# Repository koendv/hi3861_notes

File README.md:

# Hi3861 Notes

[Hi3861](https://www.hisilicon.com/en/products/smart-iot/ShortRangeWirelessIOT/Hi3861V100) is a 32-bit risc-v microcontroller, made by Huawei/HiSilicon.

- 160 MHz
- 288 kbyte rom
- 352 kbyte ram in total, 280 kbyte ram available for user programs
- 2 mbyte flash
- WiFi

## block diagram

This is a block diagram of the Hi3861 processor.
External components are a 40MHz crystal, a 32768 Hz crystal, and a pcb antenna. Flash memory is connected via spi. The HI3861 has 2 Mbyte flash memory.

The HI3861 shares die with the HI3881 wifi video camera. The HI3881 IP camera version does not have spi flash memory. The HI3881 runs software from rom.

## memory map

This is the memory map of the Hi3861. 保留 = reserved.

- RAM (rx): ORIGIN = 0x000D8000, LENGTH = 280K
- ROM  (rx):     ORIGIN = 0x003B8000, LENGTH = 288K
- FLASH (rwx):  ORIGIN = 0x00400000, LENGTH = 16M

16 Mbyte address space is mapped to spi flash, but the HI3861 spi flash is only 2 Mbyte in size.

## JTAG

## pins

pin | jtag ||
---|---|---|
IO00|JTAG_TDO|
IO01|JTAG_TCK|
IO02|JTAG_TRSTN|
IO03|JTAG_TDI|
IO04|JTAG_TMS|
IO06|JTAG_MODE|
IO08|JTAG_ENABLE|Pull high

If pin IO8 is low at power-up, pins IO0...IO4 are normal GPIO pins.
If pin IO8 is high at power-up, pins IO0...IO4 are used for JTAG.

If JTAG_ENABLE is high at power-up, pins IO03, IO04 are used for JTAG.  If JTAG_ENABLE is low at power-up, pins IO03, IO04 are used as console serial port RX, TX pins. Conflict is possible if using usb serial and JTAG at the same time.

## hi3861 start up mode

Pin|Default state|Low level|High level
---|---|---|---
IO2/REFCLK_FREQ_STATUS|Pull down|40MHz (Default) |24MHz
IO6/JTAG_MODE|Pull down|Normal function mode (Default) |DFT Test mode
IO8/JTAG_ENABLE|Pull down|Ordinary IO (Default) |JTAG enable

## jtag adapter

|||
|---|---|
|front|back|

A small circuit is needed to enable the JTAG interface. The adapter board plugs in on the back of the Hi3861 module. This adapter board can be soldered by hand.

- [schematic](hi3861-jtag/hi3861-jtag_sch.pdf)
- [kicad pcb design](hi3861-jtag)

## Boot

The boot process of Hi3861 consists with three parts: romboot, flashboot and kernel (user code, or the OS itself).

1. The fixed **romboot** verifies the **flashboot** at `FLASH_BASE`, copies the flashboot to `0x10A000` (which is actually `CPU_RAM_BASE + 200KB`) and executes. Since the first 64 bytes in the bootable image is the signature header, the actual entry is `0x10A040`
2. The **flashboot** then verifies and boots the **kernel** at `FLASH_BASE + 0xD3C0`.

## Build

A full build of LiteOS generates several images. Finally a `Hi3861_demo_allinone.bin` can be imported to the HiBurn tool to flash. Here is a flow chart of the build progress:

Though not documented, the signature header is simple. There is an open source signing tool in Python: [sign_bin.py](https://github.com/xingrz/hal_hisilicon/blob/319fce6760d25510ffae30f06c8d2190db636db2/hi3861/boot/sign_bin.py)

## tools

Tools to flash firmware: hiburn, openocd, jlink.

### hiburn

The tool to download firmware to the HI3861/HI3881 through the serial port is called **hiburn**. There is a hiburn from Huawei, and there are open source versions. These are different tools that share the same name.

- [Hiburn](tools/) is a Windows tool from Huawei for downloading firmware via the serial port.
- The Zephyr project has an [open source alternative  for Hi3861](https://github.com/xingrz/zephyr/blob/87f33dc624405e1a0e99fb78715cfd644421106b/scripts/west_commands/runners/hiburn.py).

The protocol to flash Hi3861 is a combination of a private command procotol and [Ymodem](https://en.wikipedia.org/wiki/YMODEM). Though the client side (HiBurn) is not open source, we can see how the protocol looks from the server side: [loaderboot](https://gitee.com/openharmony/device_soc_hisilicon/blob/master/hi3861v100/sdk_liteos/boot/loaderboot/common/cmd_loop.c) from the LiteOS/OpenHarmony SDK. Just like the flashboot, the entry of the loaderboot is at `0x10A040`.

For hiburn to work, LiteOS or OpenHarmony needs to contain the u-boot feature.

### openocd

The [openocd directory](openocd) contains configuration files for the open source tool [openocd](https://openocd.org/). This is what I use to download firmware to a Hi3861 board. Needs a FT2232 module, and the JTAG adapter above.

To build openocd with risc-v extensions:
```
sudo apt-get build-dep openocd
git clone https://github.com/riscv/riscv-openocd
cd riscv-openocd
./bootstrap
./configure --prefix=/opt/riscv-openocd
make
make install
```
To use openocd as gdb server:

```
/opt/riscv-openocd/bin/openocd -f ./interface/hi-ft2232d-ftdi-jtag.cfg -f ./target/hi3861-jtag.cfg
...
Info : clock speed 500 kHz
Info : JTAG tap: hi3861.cpu tap/device found: 0x0000076d (mfg: 0x3b6 (HiSilicon Technologies), part: 0x0000, ver: 0x0)
Info : [hi3861.cpu] datacount=1 progbufsize=3
Info : Disabling abstract command reads from CSRs.
Info : Examined RISC-V core; found 1 harts
Info :  hart 0: XLEN=32, misa=0x40901104
[hi3861.cpu] Target successfully examined.
Info : starting gdb server for hi3861.cpu on 3333
Info : Listening on port 3333 for gdb connections
load_bin
Info : Listening on port 6666 for tcl connections
Info : Listening on port 4444 for telnet connections
```
In another terminal:
```
/opt/riscv-binutils-gdb/bin/riscv-elf-gdb -q
(gdb) target extended-remote :3333
(gdb) file firmware.elf
(gdb) load
```
### ft2232

[FT2232HL](https://ftdichip.com/products/ft2232hl/) is an ic that interfaces between between usb and uart, jtag, swd, spi, or i2c. FT2232 is well supported by OpenOCD. The FT2232 board above has the advantage that the board has the same pinout as a Segger JLink, so you can use the same cable for both OpenOCD and JLink. [FT2232HL Board Schematic V3](ft2232hl/FT2232HL%20Board%20sch%20V3.pdf).

### jlink

The [jlink directory](jlink) contains a script for the [Segger JLink](https://www.segger.com/products/debug-probes/j-link/) debugger. This script can be modified to flash firmware to a Hi3861.

```
JLink.exe -device RISC-V -Speed 2000 -IF JTAG -jtagconf -1,-1 jlinkBurner.txt
```
Under linux:
```
 $ rlfe /opt/jlink/JLinkExe -device RV32 -if JTAG -speed 1000 -jtagconf -1,-1 -AutoConnect 1
Connecting to target via JTAG
ConfigTargetSettings() start
ConfigTargetSettings() end
TotalIRLen = ?, IRPrint = 0x..000000000000000000000000
ConfigTargetSettings() start
ConfigTargetSettings() end
TotalIRLen = 5, IRPrint = 0x01
JTAG chain detection found 1 devices:
 #0 Id: 0x0000076D, IRLen: 05, HiSilicon RV32
Debug architecture:
  RISC-V debug: 0.13
  AddrBits: 7
  DataBits: 32
  IdleClks: 5
Memory access:
  Via system bus: No
  Via ProgBuf: Yes (3 ProgBuf entries)
  Via abstract command (AAM): May be tried as last resort
DataBuf: 1 entries
  autoexec[0] implemented: Yes
Detected: RV32 core
CSR access via abs. commands: No
Temp. halted CPU for NumHWBP detection
HW instruction/data BPs: 4
Support set/clr BPs while running: No
HW data BPs trigger before execution of inst
BG memory access support: No
RISC-V identified.
J-Link>
```
jlink has a good implementation of the risc-v debug interface, but support to flash Hi3861 processors is not built in. Keep the JTAG cable short - 6cm or less.

### black magic probe

[Black magic probe](https://github.com/blackmagic-debug/blackmagic) is an open source debugger for arm processors. risc-v on bmp is part of the development sources, but not yet of the release. The Hi3861 is recognized, but support for reading and writing Hi3861 flash is missing.

## toolchain

Compile the riscv toolchain from source:

```
git clone --recursive https://github.com/riscv/riscv-gnu-toolchain
cd riscv-gnu-toolchain/
mkdir build
cd build/
../configure --prefix=/opt/riscv32 --with-arch=rv32im --with-abi=ilp32
make
```

The `riscv32-unknown-elf` toolchain works fine. The `riscv64-zephyr-elf` from [Zephyr SDK](https://github.com/zephyrproject-rtos/sdk-ng/releases/tag/v0.16.0) works fine, too (I prefer it since it runs on my MacBook Pro :p ).

The Hi3861's CPU is actually a RISC-V Privilege CPU with instruction set extension-M plus extension-C and Zicsr. While compiling with the Zephyr GCC, `-march=rv32imc` should be changed to `-march=rv32imc_zicsr`.

## gdb

gdb, the companion debugger for gcc. Build gdb for risc-v from source:

```
git clone https://github.com/riscv/riscv-binutils-gdb.git
cd riscv-binutils-gdb
patch -p1 < risc-v-gdb.patch
cd ..
mkdir build
cd build
../riscv-binutils-gdb/configure --prefix=/opt/riscv-binutils-gdb/ --target=riscv-elf --program-prefix=riscv-elf-
make all
sudo make install
```

If you start a 64-bit gdb, and connect to a 32-bit target, it may be necessary to specify architecture first:

```
(gdb) set architecture riscv:rv32
```
## operating systems

The Hi3861 is supported by two Huawei operating systems: LiteOS and OpenHarmony. There is also open source for the Zephyr RTOS and the rust language.

The sdk can be compiled with [riscv32-unknown-elf-gcc](https://device.harmonyos.com/en/docs/documentation/guide/quickstart-lite-steps-hi3861-setting-0000001105989316) or with hcc_riscv32, a patched gcc 7.3.  Compared to standard *riscv32-unknown-elf-gcc*, the hcc_riscv32 compiler has extensions for faster interrupts and more compact code:

- "compressed load-byte-unsigned" *lbu* and "store byte" *sb* instructions. Compiler option ``-Wa,-enable-c-lbu-sb``
- "long load immediate" *lli* instruction in 6 bytes, saves 2 bytes. Compiler option ``-femit-lli``
- "store multiple, increment after" *stmia* and "load multiple, increment after" *ldmia* instructions. Pushes/pops register sets on the stack in a single instruction, fast. Used in trap handler.
- merge multiple load and store instructions into "load multiple" *ldm* and "store multiple" *stm* instructions. Compiler option ``-fldm-stm-optimize``

These extensions to standard risc-v are discussed in [Perotti](doc/CARRV2020_paper_12_Perotti.pdf).

## zephyr

[xingrz](https://xingrz.me/) is porting [Zephyr RTOS to Hi3861](https://github.com/xingrz/zephyr/commits/hi3861-dev).

## rust

Rust application example for hi3861. Install rust from [rustup](https://rustup.rs/).
```
git clone https://gitee.com/luojia65/hihope-hi3861-example
cd hihope-hi3861-example
cargo build
```
Check binary:

```
$ /opt/riscv-binutils-gdb/bin/riscv-elf-objdump -f target/riscv32imac-unknown-none-elf/debug/hihope-hi3861-example
target/riscv32imac-unknown-none-elf/debug/hihope-hi3861-example:     file format elf32-littleriscv
architecture: riscv:rv32, flags 0x00000112:
EXEC_P, HAS_SYMS, D_PAGED
start address 0x00400000
```

Flash firmware. With openocd running, type:
```
/opt/riscv-binutils-gdb/bin/riscv-elf-gdb -q
(gdb) target extended-remote :3333
(gdb) file target/riscv32imac-unknown-none-elf/debug/hihope-hi3861-example
(gdb) load
Loading section .text, size 0x9fa lma 0x400000
Loading section .rodata, size 0x258 lma 0x4009fc
Start address 0x00400000, load size 3154
Transfer rate: 68 KB/sec, 1577 bytes/write.
(gdb) quit
```

## hardware

The picture above is the schematic of [this board](pictures/hi3861_module.jpg).

## proposal
Compare the schematic above in normal and in JTAG mode.

In normal mode, Hi3861 pin IO4 is serial port input RXD, and connected to CH340T pin 3 TXD, serial port output.

When pin IO8 JTAG_ENABLE is pulled high, pins IO4..IO8 are used in JTAG mode.
In JTAG mode, Hi3861 pin IO4 is  JTAG_TMS output.
This means there is a conflict: two output pins - Hi3861 pin IO4 and CH340T pin 3 - are connected together.

A possible solution is adding a resistor:

|||
|---|---|
|before|after|

This way when the usb serial port is idle, CH340T pin 3 is high and R7 acts like a 4.7k pull-up resistor, which is what signal JTAG_TMS requires. Tested with JLINK and FT2232HL.

## other hardware designs

- [reference design](http://www.hihope.org/en/) and [documentation](http://www.hihope.org/en/download/download.aspx?mtt=26)
- [Tiny-Hi3861](https://github.com/imliubo/Tiny-Hi3861). Original on [gitee](https://gitee.com/meng_guan/Tiny-Hi3861/)
- [genkipi](https://gitee.com/genkipi/devboard_device_itcast_genkipi)

Modules with in-built pcb antenna are probably easiest to use in your own designs.

- [FN-LINK 3161H-I](doc/Fn-Link_3161H-I_datasheet_V4.0_20200601.pdf)
- [AI-Thinker](https://docs.ai-thinker.com/en/hi)

## links

- [Hi3861V100 product page](https://www.hisilicon.com/en/products/smart-iot/ShortRangeWirelessIOT/Hi3861V100)
- [Hi3881 hiburn for linux](https://github.com/OpenHisiIpCam/hiburn)
- [open source hiburn for Hi3861](https://github.com/xingrz/zephyr/blob/87f33dc624405e1a0e99fb78715cfd644421106b/scripts/west_commands/runners/hiburn.py)
- [Hi3861 on aliexpress](https://www.aliexpress.com/item/1005003339044104.html)
- [Installing Liteos on Hi3861 (in Chinese)](https://harmonyos.51cto.com/posts/4013)
- [Zephyr RTOS for Hi3861](https://github.com/xingrz/zephyr/commits/hi3861-dev).
- FT2232HL [schematic](https://github.com/arm8686/FT2232HL-Board) and [shop](https://www.aliexpress.com/item/32975940318.html).

[xingrz](https://xingrz.me) provided the sections about booting, building LiteOS, Zephyr and flashing with the hiburn protocol.

This document may contain errors. If you find errors in this document, please open an issue or a pull request.
If this page saved you some time, maybe you want to buy me a cup of tea.  Thank you.

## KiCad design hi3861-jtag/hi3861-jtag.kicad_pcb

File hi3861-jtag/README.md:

This is a board to connect a jtag or swd debugger to a hi3861.

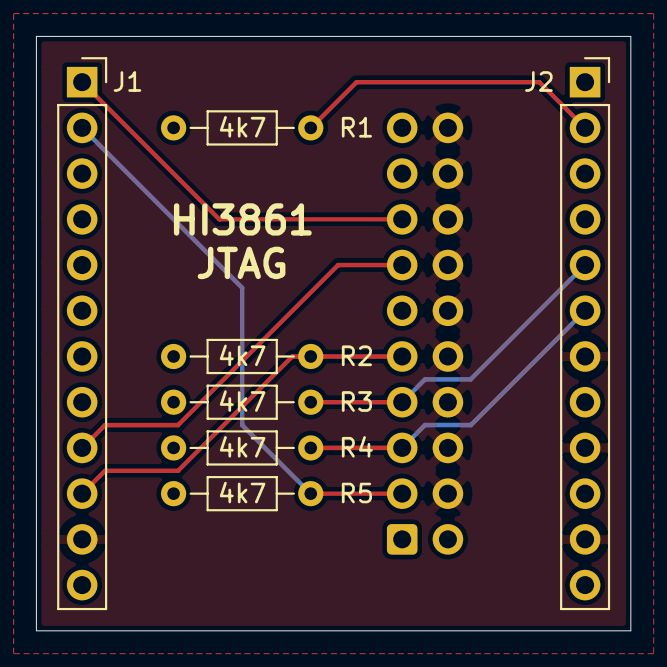
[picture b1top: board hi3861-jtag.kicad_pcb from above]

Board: 2 copper layers, 33.0 x 33.0 mm, 8 parts (1 on the bottom side), 9 nets.

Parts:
J1, J2: Conn_01x12; PinSocket_1x12_P2.54mm_Vertical
J3: Conn_ARM_JTAG_SWD_20; IDC-Header_2x10_P2.54mm_Vertical
R1, R2, R3, R4, R5: 4k7; R_Axial_DIN0204_L3.6mm_D1.6mm_P7.62mm_Horizontal

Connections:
+3V3: J1.12, J2.8, J3.1, R1.1, R2.1, R3.1, R4.1, R5.1
GND: J1.11, J2.7, J2.9, J2.11, J3.4, J3.6, J3.8, J3.10, J3.12, J3.14, J3.16, J3.18, J3.20
JTAG_EN: J2.2, R1.2
RST: J1.1, J3.15
TCK: J1.10, J3.9, R2.2
TDI: J2.6, J3.5, R4.2
TDO: J1.9, J3.13
TMS: J2.5, J3.7, R3.2
TRST: J1.2, J3.3, R5.2

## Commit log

2022-02-20 init
2022-03-01 updt
2022-03-02 gerbers
2022-03-06 xpack
2022-03-27 ft2232
2022-03-28 proposal
2022-03-30 jtag
2022-03-30 flash
2022-03-30 tested
2022-04-01 serial
2023-05-06 boot, build, flash
2023-05-07 toolchain
